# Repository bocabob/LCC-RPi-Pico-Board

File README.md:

# Raspberry Pi Pico for LCC

KiCad OpenLCB / LCC Raspberry Pi Pico motherboard for model railroad control.

Documentation, source, and gerbers for the board may be found in this repository:
<https://github.com/bocabob/LCC-RPi-Pico-Board>

## Overview

This board provides a flexible Raspberry Pi Pico (or Pico 2) platform for OpenLCB/LCC nodes. It includes:

- 3.3V and 5V switching power regulation
- Provision for onboard or plug-attached EEPROM or FRAM NVM modules
- Configurable to be powered from LCC, powered independently, or to inject power onto the LCC bus
- Tested with the OpenLCB Single Thread and OpenLcbCLib libraries

## Evolution

The LCC Pico development boards evolved from LocoNet designs dating back to 2021. The early turntable boards used Arduino Nanos and depended on turnout commands for indexing to hard-coded stepper positions. Fascia panel input was desired, so a keypad version was developed. This proved cumbersome, so a small touch screen was added with a Mega processor. The screen size needed to grow to nine inches for usability, so the Raspberry Pi Pico was selected. The Pico represents the "Goldilocks" processor of very good function, technical stability, and the easy-to-use Arduino IDE. Moving to the Pico enabled the LCC migration in 2024, when the Single Thread library began to support the RP2040 processor family. With OpenLcbCLib, full protocol support was enabled.

Earlier revisions also included a dedicated **Stepper** board with its own stepper motor driver circuitry built in. As of v3.0, that circuitry has moved to a separate breakout board that plugs into the standard Node board, so there is no longer a need for a Stepper-specific board design — one Node board now serves every node type.

## Family

There is a single board design: the **Node**. It exposes 16 GP pins through two 10P IDC connectors, plus an additional 5-pin analog header (I/O-3), for general-purpose I/O. Specialized functions — stepper motor control, displays, servos, etc. — are added via plug-in breakout boards rather than dedicated board variants.

While the board works with either the Pico or the Pico 2, the Pico 2 is recommended for its enhanced capabilities.

## Common Features

### Power

The board provides dual switching outputs of 3.3V and 5V, with input either from the LCC CAN bus or an external 8–15V source. It may be configured to inject power onto the CAN bus, or to isolate power on either or both of the CAN bus jacks. Auxiliary 3.3V and 5V outputs are available on the board.

### CAN Bus Control

Uses the discrete MCP2518 and MCP2562 CAN controller/transceiver hardware (easier to hand-solder than the integrated MCP251863 used on some earlier boards).

### Non-Volatile Memory (NVM)

I2C non-volatile memory should be used to reduce wear on the Pico flash. External NVM may be attached via the I2C header, the FRAM Breakout header, or soldered down to the IC5 footprint. When using the latter two, the I2C address jumpers may be used to select non-default addresses or implement write protection. Otherwise, those functions are handled by the module plugged into the I2C header.

Typical parts include modules using an AT25C256 chip or RC256V FRAM. Parts compatible with the following pinouts should work for soldering directly to the footprint:

- BR24G512F-3AGTE2 I2C BUS (2-Wire) 512K, or other sizes with equivalent pinouts
- MB85RC256VPF-G-BCERE1 256kbit FRAM with I2C

### I2C

I2C is used to address NVM. One or both of the available I2C channels on the Pico are exposed via headers for external devices. Care should be taken when attaching peripherals to the same channel as the NVM, to avoid interference. Some I2C devices require 5V, so a jumper selects between the two available voltages.

### Buttons

Since the Pico has no reset button, one is provided on the board. There is also a header so a remote reset button may be wired in. Provision is included for blue and gold buttons; on v3.0 these share pins with the I/O-2 and I/O-3 connectors (see pin table below), so they are unavailable when a breakout uses those specific pins.

### IDC Connections

GP pins and other connections are available on 10P IDC connectors (I/O-1, I/O-2), plus a 5-pin analog header (I/O-3). Pinouts are printed on the silkscreen and in the board user guide. On each 10P connector, pin 5 is Ground and pin 6 is a jumper-selectable voltage rail (3.3V or 5V) for the attached breakout.

## Board Variants

### LCC-Pico-Node v3.0

- MCP2518 and MCP2562 chips for CAN bus implementation of OpenLCB/LCC protocols
- Two 10-pin IDC connectors (I/O-1, I/O-2) exposing 16 GP pins for general-purpose I/O
- One 5-pin analog header (I/O-3) for additional GP/analog connections
- Two I2C ports
- Stepper, display, servo, or other specialized functions are added via plug-in breakout boards rather than being built into the Node board itself

### IDC Breakout Boards

- **Display 101 Adapter** — attaches to a BuyDisplay ER-TFTM101 10.1" touchscreen for SPI display control and I2C touch. Includes provision for alternate assignments of line 10 and a reset button.
- **Stepper Breakout** *(planned — design files not yet in this repository)* — carries a stepper motor driver and provides connections to the stepper motor, sensors, NeoPixel bus, and an I2C connection. Has a separate power connection for the external stepper motor supply (12–15V) and for the +5V used for Hall sensors and the NeoPixel bus; the IDC connector voltage should be set to 3.3V on the Node side when this breakout is attached.
- **Ribbon Breakout** — IDC breakout with optional LEDs for testing.
- **Servo Breakout** — IDC breakout with power and ground pins around each GPIO pin to facilitate connections to inputs, servos, NeoPixels, or other devices.

## Board Pin Assignments

| Pin | GP       | Alt 1     | Alt 2    | v3.0 Node                          |
|-----|----------|-----------|----------|------------------------------------|
| 1   | gp0      | SPI0 RX   | I2C0 SDA | ACAN_RX_PIN                        |
| 2   | gp1      | SPI0 CSN  | I2C0 SCL | ACAN_CS_PIN                        |
| 3   | GND      |           |          |                                     |
| 4   | gp2      | SPI0 SCK  | I2C1 SDA | ACAN_CSK_PIN                       |
| 5   | gp3      | SPI0 TX   | I2C1 SCL | ACAN_TX_PIN                        |
| 6   | gp4      | SPI0 RX   | I2C0 SDA | ACAN_INT_PIN                       |
| 7   | gp5      | SPI0 CSn  | I2C0 SCL | I/O-2: Pin 10 & Blue Button        |
| 8   | GND      |           |          |                                     |
| 9   | gp6      | SPI0 SCK  | I2C1 SDA | I2C1 SDA                           |
| 10  | gp7      | SPI0 TX   | I2C1 SCL | I2C1 SCL                           |
| 11  | gp8      | SPI1 RX   | I2C0 SDA | I/O-1: Pin 1                       |
| 12  | gp9      | SPI1 CSn  | I2C0 SCL | I/O-1: Pin 2                       |
| 13  | GND      |           |          |                                     |
| 14  | gp10     | SPI1 SCK  | I2C1 SDA | I/O-1: Pin 3                       |
| 15  | gp11     | SPI1 TX   | I2C1 SCL | I/O-1: Pin 4                       |
| 16  | gp12     | SPI1 RX   | I2C0 SDA | I/O-1: Pin 7                       |
| 17  | gp13     | SPI1 CSn  | I2C0 SCL | I/O-1: Pin 8                       |
| 18  | GND      |           |          |                                     |
| 19  | gp14     | SPI1 SCK  | I2C1 SDA | I/O-1: Pin 9                       |
| 20  | gp15     | SPI1 TX   | I2C1 SCL | I/O-1: Pin 10                      |
| 21  | gp16     | SPI0 RX   | I2C0 SDA | I/O-2: Pin 1                       |
| 22  | gp17     | SPI0 CSn  | I2C0 SCL | I/O-2: Pin 2                       |
| 23  | GND      |           |          |                                     |
| 24  | gp18     | SPI0 SCK  | I2C1 SDA | I/O-2: Pin 3                       |
| 25  | gp19     | SPI0 TX   | I2C1 SCL | I/O-2: Pin 4                       |
| 26  | gp20     |           | I2C0 SDA | I/O-2: Pin 7                       |
| 27  | gp21     |           | I2C0 SCL | I/O-2: Pin 8                       |
| 28  | GND      |           |          |                                     |
| 29  | gp22     |           |          | I/O-2: Pin 9                       |
| 30  | RUN      |           |          | Reset Button / header              |
| 31  | gp26     | ADC0      | I2C1 SDA | I/O-3: Pin 1                       |
| 32  | gp27     | ADC1      | I2C1 SCL | I/O-3: Pin 2                       |
| 33  | GND      | A GND     |          | I/O-3: Pin 3 (AGND)                |
| 34  | gp28     | ADC2      |          | I/O-3: Pin 5 & Gold Button         |
| 35  |          | ADC_VREF  |          | I/O-3: Pin 4 (VREF)                |
| 36  | 3v3_OUT  |           |          |                                     |
| 37  | 3V3_EN   |           |          |                                     |
| 38  | GND      |           |          |                                     |
| 39  | VSYS     |           |          |                                     |
| 40  | VBUS     |           |          |                                     |
|     | GND      |           |          | I/O-1: Pin 5                       |
|     | Vselect1 |           |          | I/O-1: Pin 6                       |
|     | GND      |           |          | I/O-2: Pin 5                       |
|     | Vselect2 |           |          | I/O-2: Pin 6                       |

Note: I/O-2 Pin 10 (gp5) and I/O-3 Pin 5 (gp28) double as the Blue and Gold buttons. A breakout that uses either of those pins makes the corresponding button unavailable.

## Software

### Example Node Applications

- <https://github.com/bocabob/LCC_RPiPico_Turntable>
- <https://github.com/bocabob/LCC_RPiPico_Roundhouse>
- <https://github.com/bocabob/LCC_RPiPico_PixelLights>
- <https://github.com/bocabob/LCC_RPiPico_Clock_Lights>

### Architectural Standard

Cross-project firmware conventions (board versioning, breakout pin assignments, configuration memory, naming) for all node applications above are documented in:
<https://github.com/bocabob/LCC_RPiPico_Common>

### Board Support

Use the RP2040 board library by Earle Philhower:
<https://arduino-pico.readthedocs.io/en/latest/install.html>

### LCC Support

- <https://github.com/openlcb/OpenLCB_Single_Thread>
- <https://github.com/JimKueneman/OpenLcbCLib>

### CAN Hardware

- ACAN2517 Arduino library

### External Storage

- I2C_EEPROM Arduino library by Rob Tillaart
- FRAM_I2C Arduino library by Rob Tillaart

### NeoPixel

- NeoPixelBus by Makuna (preferred)
- NeoPixelConnect by Alan Yorinks

### Other Preferred Libraries

#### Display

- `TFT_eSPI_RA8876.h` — display library (modified): <https://github.com/bocabob/TFT_eSPI_RA8876>
- `RA8876_RP2040.h` — display library (modified): <https://github.com/bocabob/RA8876_RP2040>
- `my_bb_captouch.h` — capacitive touch driver (modified): <https://github.com/bocabob/my_bb_captouch>

#### Servos

- `ServoEasing.hpp` — for slow servo action, including bounces
- `PCA9685_servo_driver.h`
- `PCA9685_servo.h`

#### Stepper Motor

- `AccelStepper.h` by Mike McCauley (modified)

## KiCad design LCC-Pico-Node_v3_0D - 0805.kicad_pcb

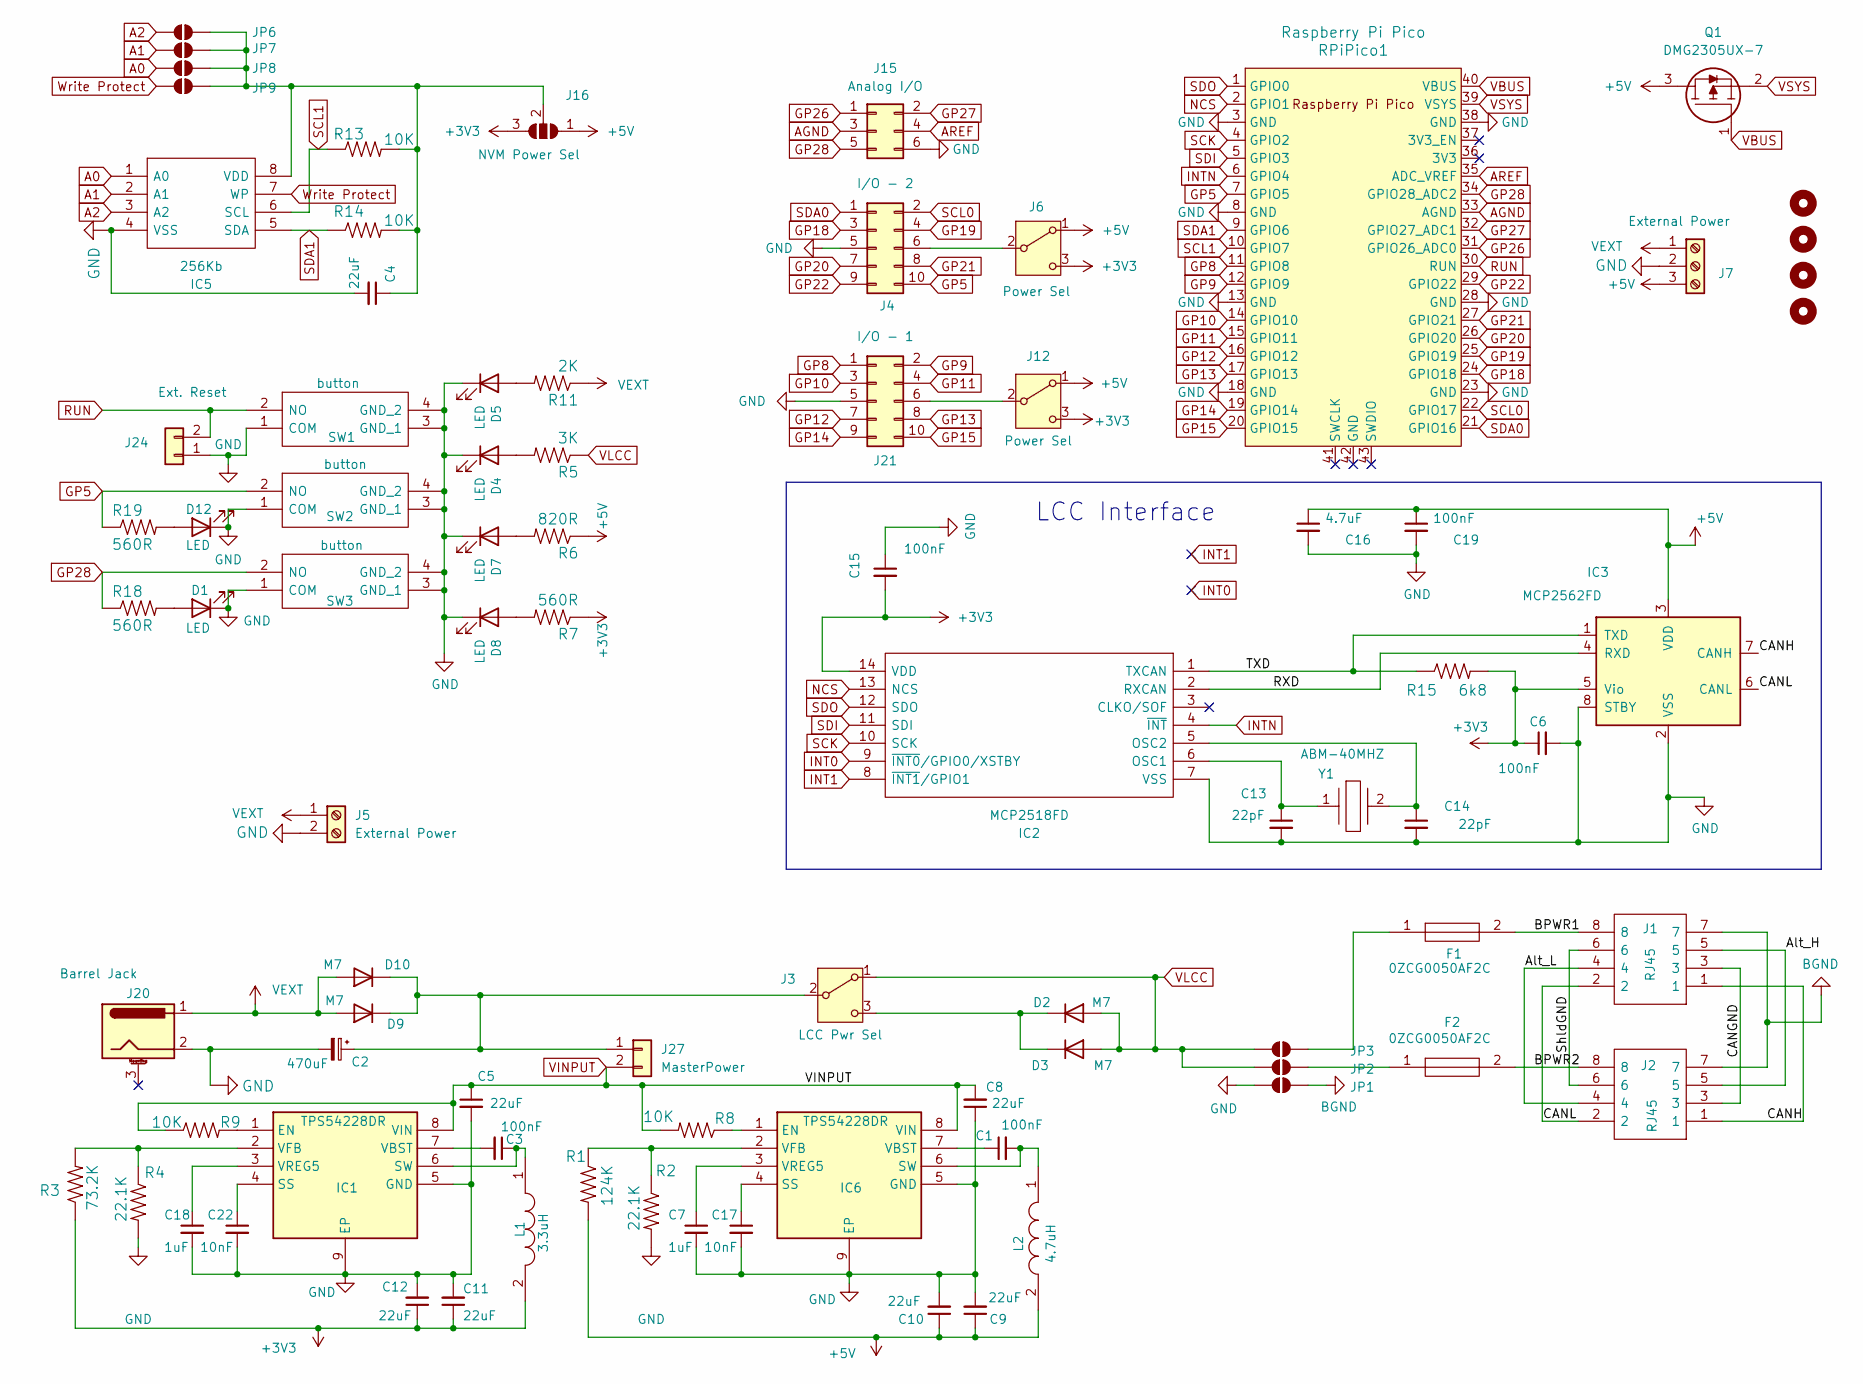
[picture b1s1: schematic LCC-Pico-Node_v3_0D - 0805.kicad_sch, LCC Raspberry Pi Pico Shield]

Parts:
C1, C3, C6, C15, C19: 100nF; C_0805_2012Metric; LCSC C49678
C2: 470uF; CP_Elec_8x10.5; LCSC C48935389
C4, C5, C8, C9, C10, C11, C12: 22uF; C_0805_2012Metric; LCSC C45783
C7, C18: 1uF; C_0805_2012Metric; LCSC C28323
C13, C14: 22pF; C_0805_2012Metric; LCSC C1804
C16: 4.7uF; C_0805_2012Metric; LCSC C1779
C17, C22: 10nF; C_0805_2012Metric; LCSC C1710
D1, D4, D5, D7, D8, D12: LED; LED_0805_2012Metric; LCSC C2297
D2, D3, D9, D10: M7; D_SMA; LCSC C22448047
F1, F2: 0ZCG0050AF2C; FUSC4632X70N; Mouser Part Number 530-0ZCG0050AF2C
H1, H2, H3, H4: MountingHole; MountingHole_3.2mm_M3
IC1, IC6: TPS54228DR; SOIC127P600X170-9N; Mouser Part Number 595-TPS54228DDAR
IC2: MCP2518FD; SOIC-14_3.9x8.7mm_P1.27mm; Mouser Part Number 579-MCP2518FDT-E/SL
IC3: MCP2562FD; SOIC-8_3.9x4.9mm_P1.27mm; Mouser Part Number 771-TJA1042T/3/1J
IC5: 256Kb; SOIC127P600X175-8N; Mouser Part Number 755-BR24G256F-5E2
J1, J2: RJ45; MTJ880X1; Mouser Part Number 737-MTJ-880X1
J3: LCC Pwr Sel; SLW8645872ARAND
J4: I/O - 2; IDC-Header_2x05_P2.54mm_Vertical
J5: External Power; PhoenixContact_MSTBA_2,5_2-G-5,08_1x02_P5.08mm_Horizontal
J6, J12: Power Sel; SLW8645872ARAND
J7: External Power; JST_EH_B3B-EH-A_1x03_P2.50mm_Vertical
J15: Analog I/O; IDC-Header_2x03_P2.54mm_Vertical
J16: NVM Power Sel; SolderJumper-3_P1.3mm_Open_RoundedPad1.0x1.5mm
J20: Barrel Jack; DC-050_SMD; LCSC C431534
J21: I/O - 1; IDC-Header_2x05_P2.54mm_Vertical
J24: Ext. Reset; PinHeader_1x02_P2.54mm_Vertical
J27: MasterPower; PinHeader_1x02_P2.54mm_Vertical
JP1: GND; SolderJumper-2_P1.3mm_Bridged_RoundedPad1.0x1.5mm
JP2: CAN2; SolderJumper-2_P1.3mm_Open_RoundedPad1.0x1.5mm
JP3: CAN1; SolderJumper-2_P1.3mm_Open_RoundedPad1.0x1.5mm
JP6: A2; SolderJumper-2_P1.3mm_Open_Pad1.0x1.5mm
JP7: A1; SolderJumper-2_P1.3mm_Open_Pad1.0x1.5mm
JP8: A0; SolderJumper-2_P1.3mm_Open_Pad1.0x1.5mm
JP9: WP; SolderJumper-2_P1.3mm_Open_Pad1.0x1.5mm
L1: 3.3uH; L_1210_3225Metric; Mouser Part Number 81-1277AS-H-3R3MP2
L2: 4.7uH; L_1210_3225Metric; Mouser Part Number 81-1276AS-H-4R7MP2
Q1: DMG2305UX-7; SOT96P240X115-3N; Mouser Part Number 621-DMG2305UX-7
R1: 124K; R_0805_2012Metric; LCSC C2902861
R2, R4: 22.1K; R_0805_2012Metric; LCSC C865310
R3: 73.2K; R_0805_2012Metric; LCSC C422816
R5: 3K; R_0805_2012Metric; LCSC C17661
R6: 820R; R_0805_2012Metric; LCSC C17837
R7, R18, R19: 560R; R_0805_2012Metric; LCSC C28636
R8, R9, R13, R14: 10K; R_0805_2012Metric; LCSC C17414
R11: 2K; R_0805_2012Metric; LCSC C17604
R15: 6k8; R_0805_2012Metric; LCSC C17772
RPiPico1: Raspberry Pi Pico; RPi_Pico_SMD_TH; PARTREV 12/May/2017
SW1, SW2, SW3: button; SW_Push_1P1T_XKB_TS-1187A; Mouser Part Number 179-TS1167443160RAD
Y1: ABM-40MHZ; ABM3; Mouser Part Number 815-ABL-40-B2F

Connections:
+3V3: C6.1, C11.1, C12.1, C15.2, IC2.14 (VDD), IC3.5 (Vio), J6.3 (C), J12.3 (C), J16.3 (B), L1.2, R3.1, R7.1, R15.2
+5V: C9.1, C10.1, C16.1, C19.1, IC3.3 (VDD), J6.1 (A), J7.3, J12.1 (A), J16.1 (A), L2.2, Q1.3, R1.2, R6.1
/Alt_H: J1.5, J2.5
/Alt_L: J1.4, J2.4
/BPWR1: F1.2, J1.8
/BPWR2: F2.2, J2.8
/CANGND: J1.3, J2.3
/CANH: IC3.7 (CANH), J1.1, J2.1
/CANL: IC3.6 (CANL), J1.2, J2.2
/RXD: IC2.2 (RXCAN), IC3.4 (RXD)
/ShldGND: J1.6, J2.6
/TXD: IC2.1 (TXCAN), IC3.1 (TXD), R15.1
A0: IC5.1 (A0), JP8.1 (A)
A1: IC5.2 (A1), JP7.1 (A)
A2: IC5.3 (A2), JP6.1 (A)
AGND: J15.3, RPiPico1.33 (AGND)
AREF: J15.4, RPiPico1.35 (ADC_VREF)
BGND: J1.7, J2.7, JP1.2 (B)
GND: C2.2, C4.2, C5.2, C6.2, C7.2, C8.1, C9.2, C10.2, C11.2, C12.2, C13.2, C14.2, C15.1, C16.2, C17.2, C18.2, C19.2, C22.2, D1.1 (K), D4.1 (K), D5.1 (K), D7.1 (K), D8.1 (K), D12.1 (K), IC1.5 (GND), IC1.9 (EP), IC2.7 (VSS), IC3.2 (VSS), IC3.8 (STBY), IC5.4 (VSS), IC6.5 (GND), IC6.9 (EP), J4.5, J5.2, J7.2, J15.6, J20.2, J21.5, J24.1, JP1.1 (A), R2.2, R4.2, RPiPico1.3 (GND), RPiPico1.8 (GND), RPiPico1.13 (GND), RPiPico1.18 (GND), RPiPico1.23 (GND), RPiPico1.28 (GND), RPiPico1.38 (GND), SW1.1 (COM), SW1.3 (GND_1), SW1.4 (GND_2), SW2.1 (COM), SW2.3 (GND_1), SW2.4 (GND_2), SW3.1 (COM), SW3.3 (GND_1), SW3.4 (GND_2)
GP5: J4.10, R19.1, RPiPico1.7 (GPIO5), SW2.2 (NO)
GP8: J21.1, RPiPico1.11 (GPIO8)
GP9: J21.2, RPiPico1.12 (GPIO9)
GP10: J21.3, RPiPico1.14 (GPIO10)
GP11: J21.4, RPiPico1.15 (GPIO11)
GP12: J21.7, RPiPico1.16 (GPIO12)
GP13: J21.8, RPiPico1.17 (GPIO13)
GP14: J21.9, RPiPico1.19 (GPIO14)
GP15: J21.10, RPiPico1.20 (GPIO15)
GP18: J4.3, RPiPico1.24 (GPIO18)
GP19: J4.4, RPiPico1.25 (GPIO19)
GP20: J4.7, RPiPico1.26 (GPIO20)
GP21: J4.8, RPiPico1.27 (GPIO21)
GP22: J4.9, RPiPico1.29 (GPIO22)
GP26: J15.1, RPiPico1.31 (GPIO26_ADC0)
GP27: J15.2, RPiPico1.32 (GPIO27_ADC1)
GP28: J15.5, R18.1, RPiPico1.34 (GPIO28_ADC2), SW3.2 (NO)
INT0: IC2.9 (~INT0/GPIO0/XSTBY)
INT1: IC2.8 (~INT1/GPIO1)
INTN: IC2.4 (~INT), RPiPico1.6 (GPIO4)
NCS: IC2.13 (NCS), RPiPico1.2 (GPIO1)
unnamed: D1.2 (A), R18.2
unnamed: D2.1 (K), D3.1 (K), J3.3 (C)
unnamed: D4.2 (A), R5.2
unnamed: D5.2 (A), R11.2
unnamed: D7.2 (A), R6.2
unnamed: D8.2 (A), R7.2
unnamed: C2.1, D9.1 (K), D10.1 (K), J3.2 (B), J27.1
unnamed: D12.2 (A), R19.2
unnamed: IC1.1 (EN), R9.2
unnamed: C22.1, IC1.4 (SS)
unnamed: C3.1, IC1.6 (SW), L1.1
unnamed: C3.2, IC1.7 (VBST)
unnamed: IC1.2 (VFB), R3.2, R4.1
unnamed: C18.1, IC1.3 (VREG5)
unnamed: C13.1, IC2.6 (OSC1), Y1.1
unnamed: C14.1, IC2.5 (OSC2), Y1.2
unnamed: C4.1, IC5.8 (VDD), J16.2 (C), JP6.2 (B), JP7.2 (B), JP8.2 (B), JP9.2 (B), R13.2, R14.2
unnamed: IC6.1 (EN), R8.1
unnamed: C17.1, IC6.4 (SS)
unnamed: C1.2, IC6.6 (SW), L2.1
unnamed: C1.1, IC6.7 (VBST)
unnamed: IC6.2 (VFB), R1.1, R2.1
unnamed: C7.1, IC6.3 (VREG5)
unnamed: J4.6, J6.2 (B)
unnamed: J12.2 (B), J21.6
unnamed: F2.1, JP2.2 (B)
unnamed: F1.1, JP3.2 (B)
RUN: J24.2, RPiPico1.30 (RUN), SW1.2 (NO)
SCK: IC2.10 (SCK), RPiPico1.4 (GPIO2)
SCL0: J4.2, RPiPico1.22 (GPIO17)
SCL1: IC5.6 (SCL), R13.1, RPiPico1.10 (GPIO7)
SDA0: J4.1, RPiPico1.21 (GPIO16)
SDA1: IC5.5 (SDA), R14.1, RPiPico1.9 (GPIO6)
SDI: IC2.11 (SDI), RPiPico1.5 (GPIO3)
SDO: IC2.12 (SDO), RPiPico1.1 (GPIO0)
VBUS: Q1.1, RPiPico1.40 (VBUS)
VEXT: D9.2 (A), D10.2 (A), J5.1, J7.1, J20.1, R11.1
VINPUT: C5.1, C8.2, IC1.8 (VIN), IC6.8 (VIN), J27.2, R8.2, R9.1
VLCC: D2.2 (A), D3.2 (A), J3.1 (A), JP2.1 (A), JP3.1 (A), R5.1
VSYS: Q1.2, RPiPico1.39 (VSYS)
Write Protect: IC5.7 (WP), JP9.1 (A)

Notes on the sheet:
LCC Interface

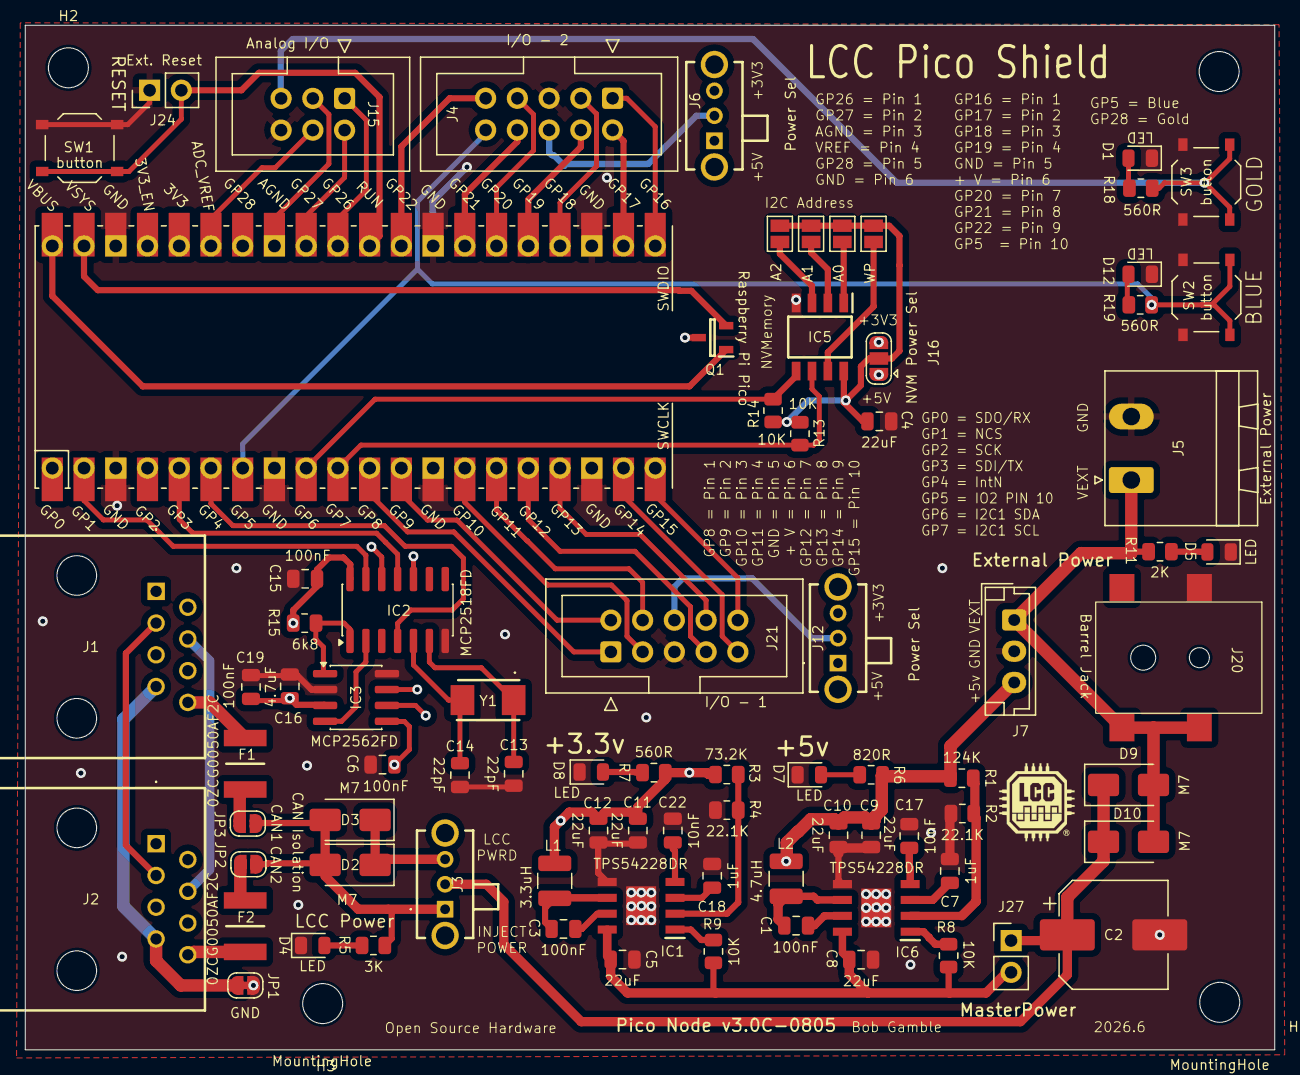
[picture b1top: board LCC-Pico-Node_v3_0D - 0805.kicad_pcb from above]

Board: 4 copper layers, 100.0 x 82.0 mm, 85 parts (0 on the bottom side), 79 nets.

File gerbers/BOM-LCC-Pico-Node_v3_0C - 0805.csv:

Comment,Designator,Footprint,LCSC,Quantity
0ZCG0050AF2C,"F1,F2",FUSC4632X70N,C3762102,2
100nF,"C1,C15,C19,C3,C6",C_0805_2012Metric,C49678,5
10K,"R13,R14,R8,R9",R_0805_2012Metric,C17414,4
10nF,"C17,C22",C_0805_2012Metric,C1710,2
124K,R1,R_0805_2012Metric,C2902861,1
1uF,"C18,C7",C_0805_2012Metric,C28323,2
22.1K,"R2,R4",R_0805_2012Metric,C865310,2
22pF,"C13,C14",C_0805_2012Metric,C1804,2
22uF,"C10,C11,C12,C4,C5,C8,C9",C_0805_2012Metric,C45783,7
256Kb,IC5,SOIC127P600X175-8N,C90485,1
2K,R11,R_0805_2012Metric,C17604,1
3.3uH,L1,L_1210_3225Metric,C337905,1
3K,R5,R_0805_2012Metric,C17661,1
4.7uF,C16,C_0805_2012Metric,C1779,1
4.7uH,L2,L_1210_3225Metric,C1330201,1
470uF,C2,CP_Elec_8x10.5,C48935389,1
560R,"R18,R19,R7",R_0805_2012Metric,C28636,3
6k8,R15,R_0805_2012Metric,C17772,1
73.2K,R3,R_0805_2012Metric,C422816,1
820R,R6,R_0805_2012Metric,C17837,1
ABM-40MHZ,Y1,ABM3,C1986264,1
DMG2305UX-7,Q1,SOT96P240X115-3N,C150470,1
LED,"D1,D12,D4,D5,D7,D8",LED_0805_2012Metric,C2297,6
M7,"D10,D2,D3,D9",D_SMA,C22448047,4
MCP2518FD,IC2,SOIC-14_3.9x8.7mm_P1.27mm,C626758,1
MCP2562FD,IC3,SOIC-8_3.9x4.9mm_P1.27mm,C511335,1
TPS54228DR,"IC1,IC6",SOIC127P600X170-9N,C263275,2
button,"SW1,SW2,SW3",SW_Push_1P1T_XKB_TS-1187A,C318884,3

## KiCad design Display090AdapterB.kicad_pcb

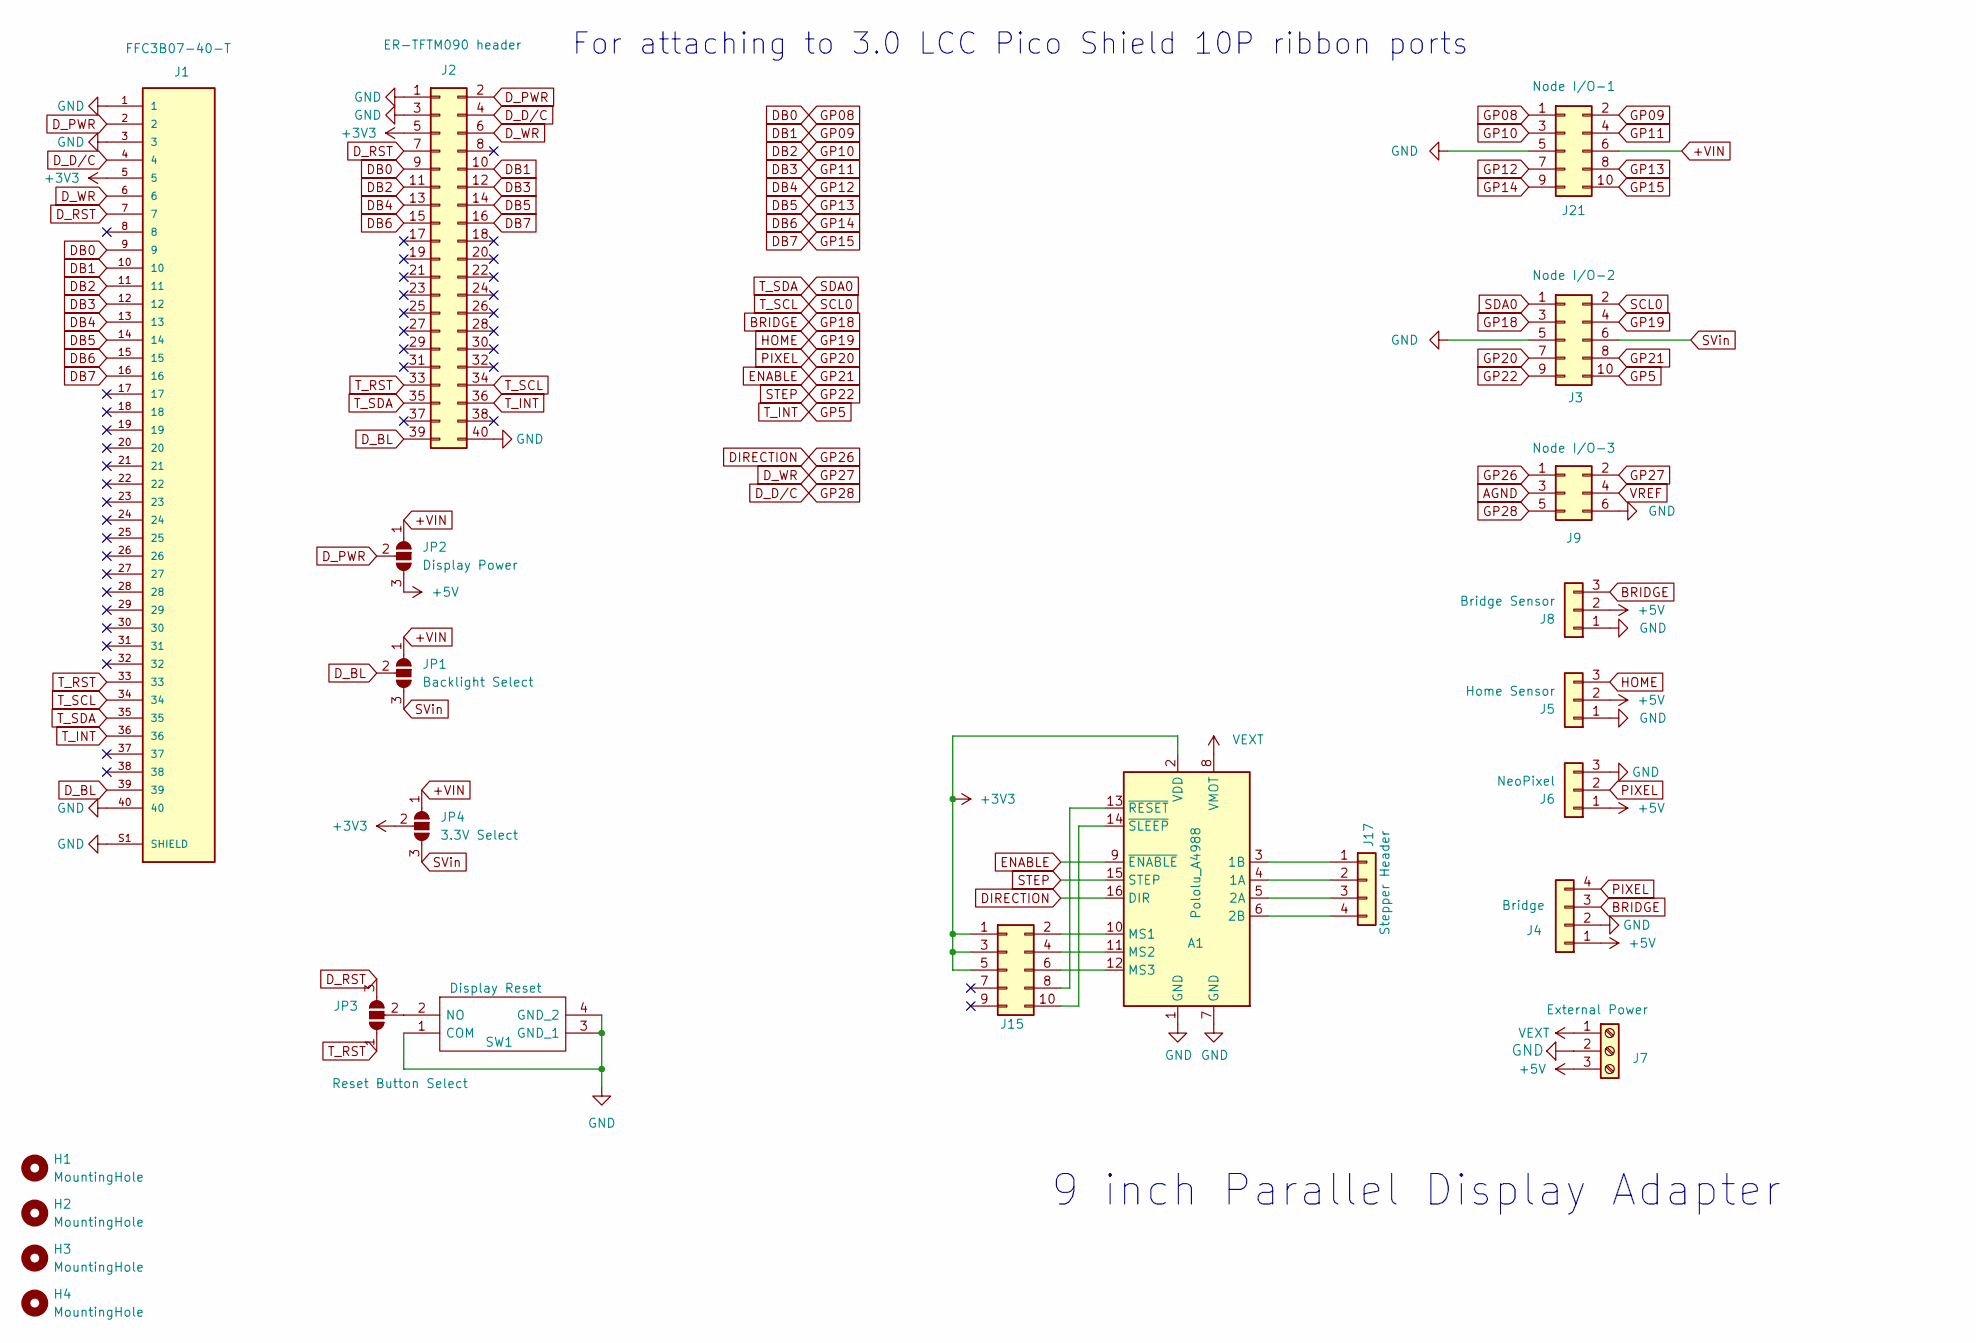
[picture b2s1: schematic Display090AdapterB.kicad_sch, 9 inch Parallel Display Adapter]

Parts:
A1: Pololu_A4988; Pololu_Breakout-16_15.2x20.3mm
H1, H2, H3, H4: MountingHole; MountingHole_3.5mm
J1: FFC3B07-40-T; GCT_FFC3B07-40-T; PARTREV A
J2: ER-TFTM090 header; PinSocket_2x20_P2.54mm_Vertical
J3: Node I/O-2; IDC-Header_2x05_P2.54mm_Vertical
J4: Bridge; PinHeader_1x04_P2.54mm_Vertical
J5: Home Sensor; JST_EH_B3B-EH-A_1x03_P2.50mm_Vertical
J6: NeoPixel; JST_EH_B3B-EH-A_1x03_P2.50mm_Vertical
J7: External Power; JST_EH_B3B-EH-A_1x03_P2.50mm_Vertical
J8: Bridge Sensor; JST_EH_B3B-EH-A_1x03_P2.50mm_Vertical
J9: Node I/O-3; IDC-Header_2x03_P2.54mm_Vertical
J15: Conn_02x05_Odd_Even; PinHeader_2x05_P2.54mm_Vertical
J17: Stepper Header; PinSocket_1x04_P2.54mm_Vertical
J21: Node I/O-1; IDC-Header_2x05_P2.54mm_Vertical
JP1: Backlight Select; SolderJumper-3_P1.3mm_Open_Pad1.0x1.5mm_NumberLabels
JP2: Display Power; SolderJumper-3_P1.3mm_Open_Pad1.0x1.5mm_NumberLabels
JP3: Reset Button Select; SolderJumper-3_P1.3mm_Open_Pad1.0x1.5mm_NumberLabels
JP4: 3.3V Select; SolderJumper-3_P1.3mm_Open_Pad1.0x1.5mm_NumberLabels
SW1: Display Reset; TS1167443BK160RAD; Mouser Part Number 179-TS1167443160RAD

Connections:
+3V3: A1.2 (VDD), J1.5, J2.5, J15.1, J15.3, J15.5, JP4.2 (C)
+5V: J4.1, J5.2, J6.1, J7.3, J8.2, JP2.3 (B)
+VIN: J21.6, JP1.1 (A), JP2.1 (A), JP4.1 (A)
AGND: J9.3
BRIDGE: J3.3, J4.3, J8.3
DB0: J1.9, J2.9, J21.1
DB1: J1.10, J2.10, J21.2
DB2: J1.11, J2.11, J21.3
DB3: J1.12, J2.12, J21.4
DB4: J1.13, J2.13, J21.7
DB5: J1.14, J2.14, J21.8
DB6: J1.15, J2.15, J21.9
DB7: J1.16, J2.16, J21.10
DIRECTION: A1.16 (DIR), J9.1
D_BL: J1.39, J2.39, JP1.2 (C)
D_D/C: J1.4, J2.4, J9.5
D_PWR: J1.2, J2.2, JP2.2 (C)
D_RST: J1.7, J2.7, JP3.3 (B)
D_WR: J1.6, J2.6, J9.2
ENABLE: A1.9 (~ENABLE), J3.8
GND: A1.1 (GND), A1.7 (GND), J1.1, J1.3, J1.40, J1.S1 (SHIELD), J1.S2 (SHIELD), J2.1, J2.3, J2.40, J3.5, J4.2, J5.1, J6.3, J7.2, J8.1, J9.6, J21.5, SW1.1 (COM), SW1.3 (GND_1), SW1.4 (GND_2)
GP5: J1.36, J2.36, J3.10
GP19: J3.4, J5.3
GP20: J3.7, J4.4, J6.2
GP22: A1.15 (STEP), J3.9
unnamed: A1.4 (1A), J17.2
unnamed: A1.3 (1B), J17.1
unnamed: A1.5 (2A), J17.3
unnamed: A1.6 (2B), J17.4
unnamed: A1.10 (MS1), J15.2
unnamed: A1.11 (MS2), J15.4
unnamed: A1.12 (MS3), J15.6
unnamed: A1.13 (~RESET), J15.8
unnamed: A1.14 (~SLEEP), J15.10
unnamed: JP3.2 (C), SW1.2 (NO)
SCL0: J1.34, J2.34, J3.2
SDA0: J1.35, J2.35, J3.1
SVin: J3.6, JP1.3 (B), JP4.3 (B)
T_RST: J1.33, J2.33, JP3.1 (A)
VEXT: A1.8 (VMOT), J7.1
VREF: J9.4

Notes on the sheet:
9 inch Parallel Display Adapter
For attaching to 3.0 LCC Pico Shield 10P ribbon ports

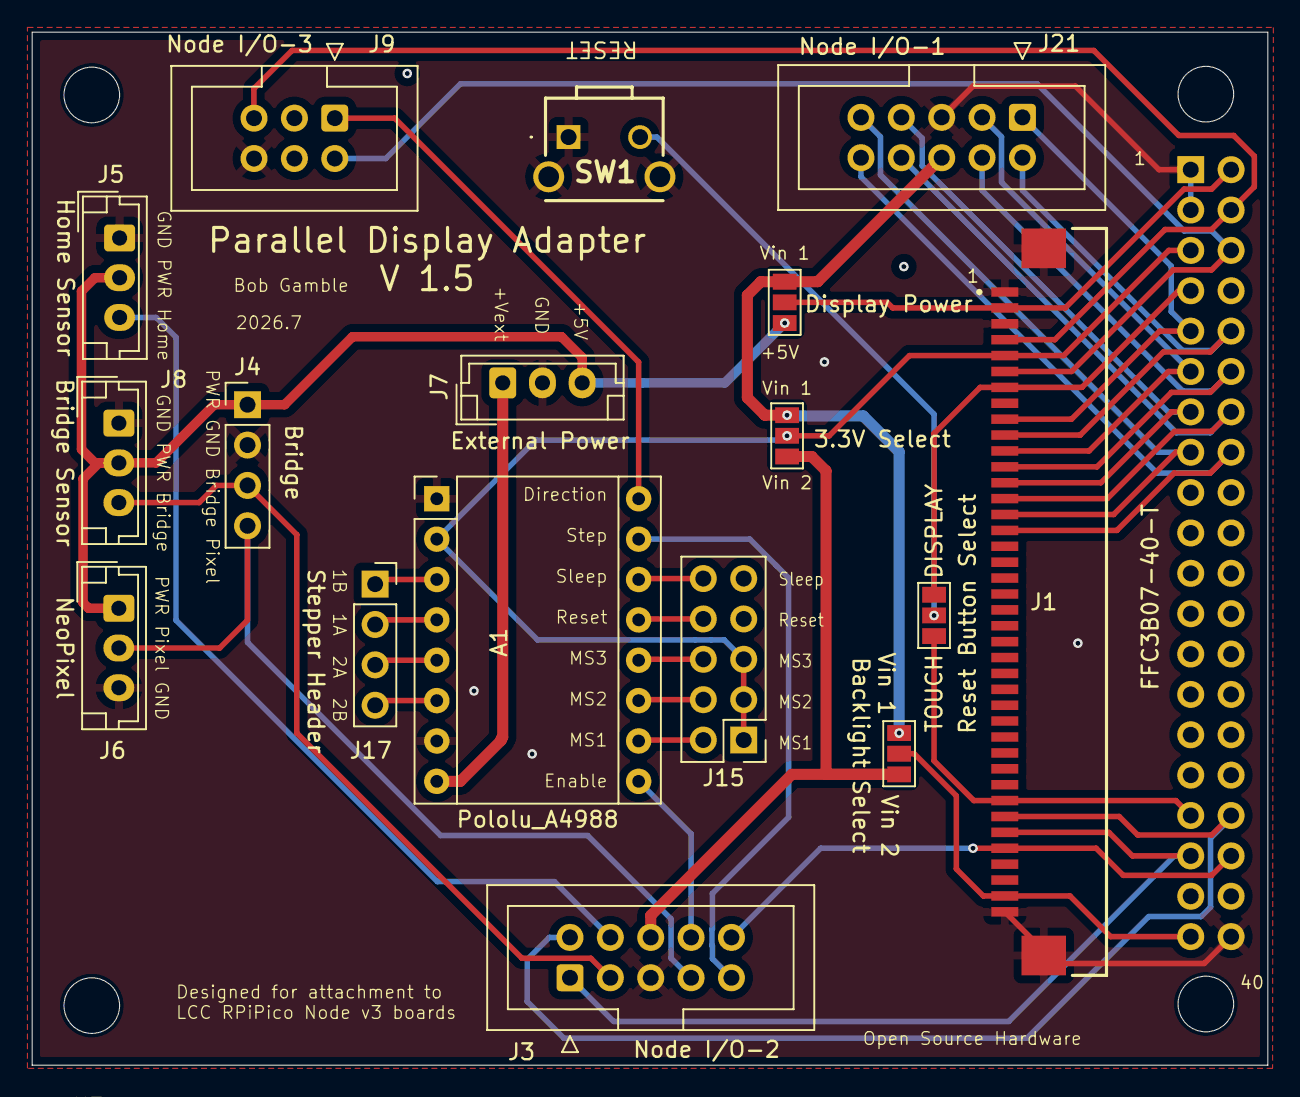
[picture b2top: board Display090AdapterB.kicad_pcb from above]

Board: 2 copper layers, 77.8 x 65.0 mm, 22 parts (1 on the bottom side), 39 nets.

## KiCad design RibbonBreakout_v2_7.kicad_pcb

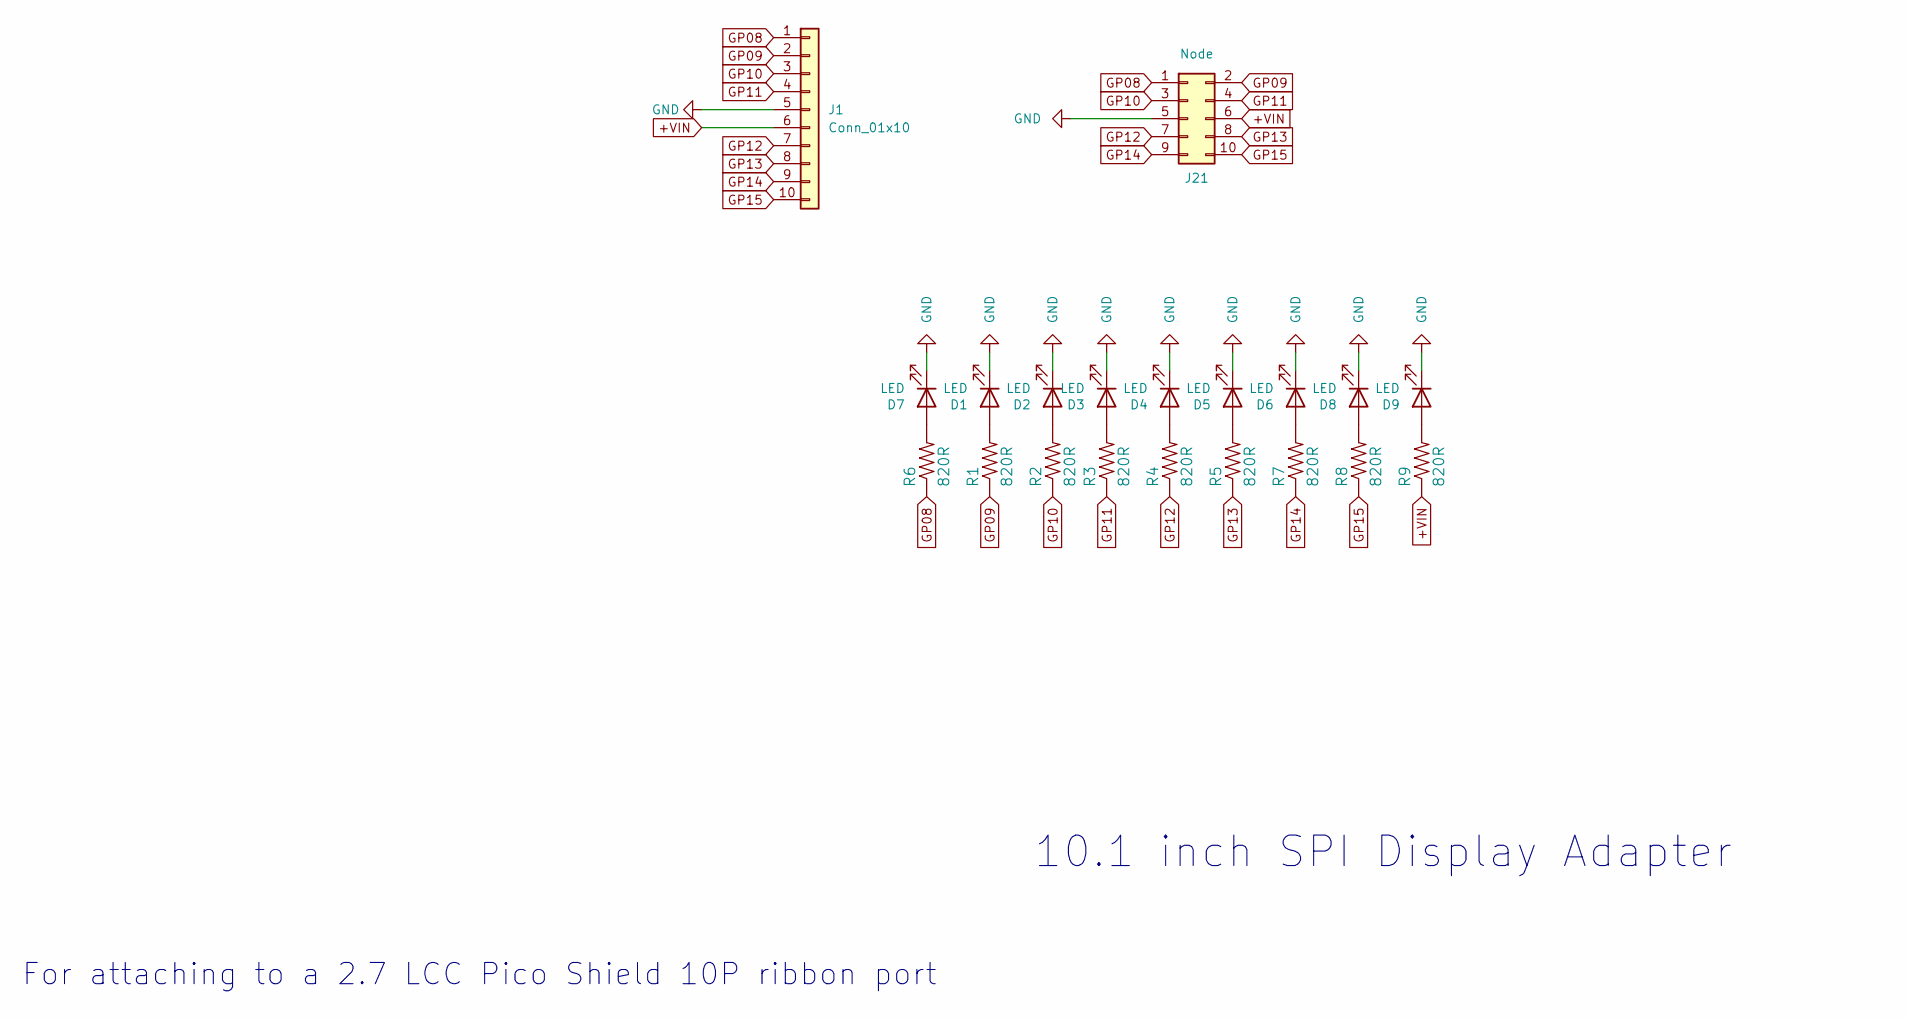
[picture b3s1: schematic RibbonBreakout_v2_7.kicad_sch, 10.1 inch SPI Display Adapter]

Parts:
D1, D2, D3, D4, D5, D6, D7, D8, D9: LED; LED_1206_3216Metric_Pad1.42x1.75mm_HandSolder
J1: Conn_01x10; PinHeader_1x10_P2.54mm_Vertical
J21: Node; IDC-Header_2x05_P2.54mm_Vertical
R1, R2, R3, R4, R5, R6, R7, R8, R9: 820R; R_1206_3216Metric_Pad1.30x1.75mm_HandSolder

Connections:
+VIN: J1.6, J21.6, R9.1
GND: D1.1 (K), D2.1 (K), D3.1 (K), D4.1 (K), D5.1 (K), D6.1 (K), D7.1 (K), D8.1 (K), D9.1 (K), J1.5, J21.5
GP08: J1.1, J21.1, R6.1
GP09: J1.2, J21.2, R1.1
GP10: J1.3, J21.3, R2.1
GP11: J1.4, J21.4, R3.1
GP12: J1.7, J21.7, R4.1
GP13: J1.8, J21.8, R5.1
GP14: J1.9, J21.9, R7.1
GP15: J1.10, J21.10, R8.1
unnamed: D1.2 (A), R1.2
unnamed: D2.2 (A), R2.2
unnamed: D3.2 (A), R3.2
unnamed: D4.2 (A), R4.2
unnamed: D5.2 (A), R5.2
unnamed: D6.2 (A), R7.2
unnamed: D7.2 (A), R6.2
unnamed: D8.2 (A), R8.2
unnamed: D9.2 (A), R9.2

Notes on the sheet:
10.1 inch SPI Display Adapter
For attaching to a 2.7 LCC Pico Shield 10P ribbon port

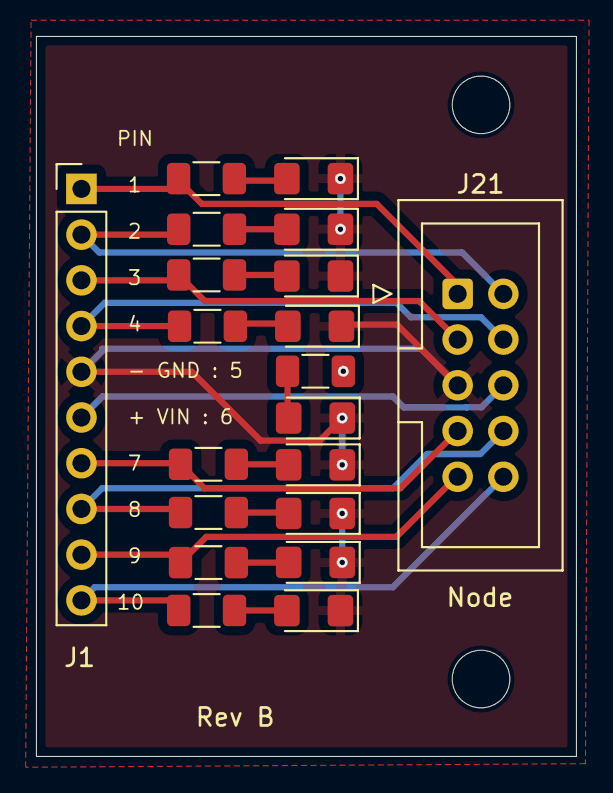
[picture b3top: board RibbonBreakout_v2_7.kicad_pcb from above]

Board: 2 copper layers, 30.0 x 40.0 mm, 20 parts (0 on the bottom side), 19 nets.
